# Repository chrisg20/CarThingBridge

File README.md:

# CarThingBridge
A compact connector board for the Spotify Car Thing and Raspberry Pi Zero, for use with [Nocturne](https://github.com/usenocturne/nocturne-image).

3D printed mount on Printables [here](https://www.printables.com/model/1098732-car-thing-pi-bridge).

# Ordering Instructions
I no longer sell the boards due to lower demand, high tariffs, etc. 

If you want one, it is worth asking on the Nocturne Discord server to see if other users have extra boards that they would be willing to give or sell to you. 

Server: https://discord.gg/GTP9AawHPt

To order boards yourself, follow these steps:

**Order PCB Only (Manual Assembly)**

Manual assembly should only be attempted if you are experienced in soldering very small (0603) components.

* Download the ZIP archive: https://github.com/chrisg20/CarThingBridge/PCB/production/.
* Visit https://JLCPCB.com and click Order Now.
* Upload Bridge_v1.zip from the PCB/production/ directory.
* VERY IMPORTANT! Set PCB Layers to 2 and Thickness to 0.8mm — this is required for the straddle-mounted USB-C connector.
* Order components from Digi-Key, Mouser, etc.
* Required Components (per PCB):
  * CX60-24S-UNIT (x1)
  * CX90M-16P (x1)
  * SSSS811101 (x1)
  * ZX60-B-5S(31) (x2)
  * 0603WAF5101T5E (x3)

**Order PCB with Assembly**

* Enable PCB Assembly during order setup.
* On the Bill of Materials page:
* Upload bom.csv from PCB/production/.
* Upload positions.csv from PCB/production/.
* Review the component placement preview to ensure it looks correct.

You will receive the a notification to pay an additional ~$50 for a fixture required for the USB-C connector (C5338340).

# Instructions

Print the mount and install 4 M2.5x3mm inserts into the holes. Place adhesive strips into the slots and attach to the car thing so that the Nocturne logo bar lines up with the left edge of the Car Thing as shown in the image below.

Connect the Raspberry Pi to the bridge and the bridge to the Car Thing. Secure the Raspberry Pi to the mount with 4 M2.5x4mm screws. Ensure the small switch is set to ON (away from the Raspberry Pi) as shown.

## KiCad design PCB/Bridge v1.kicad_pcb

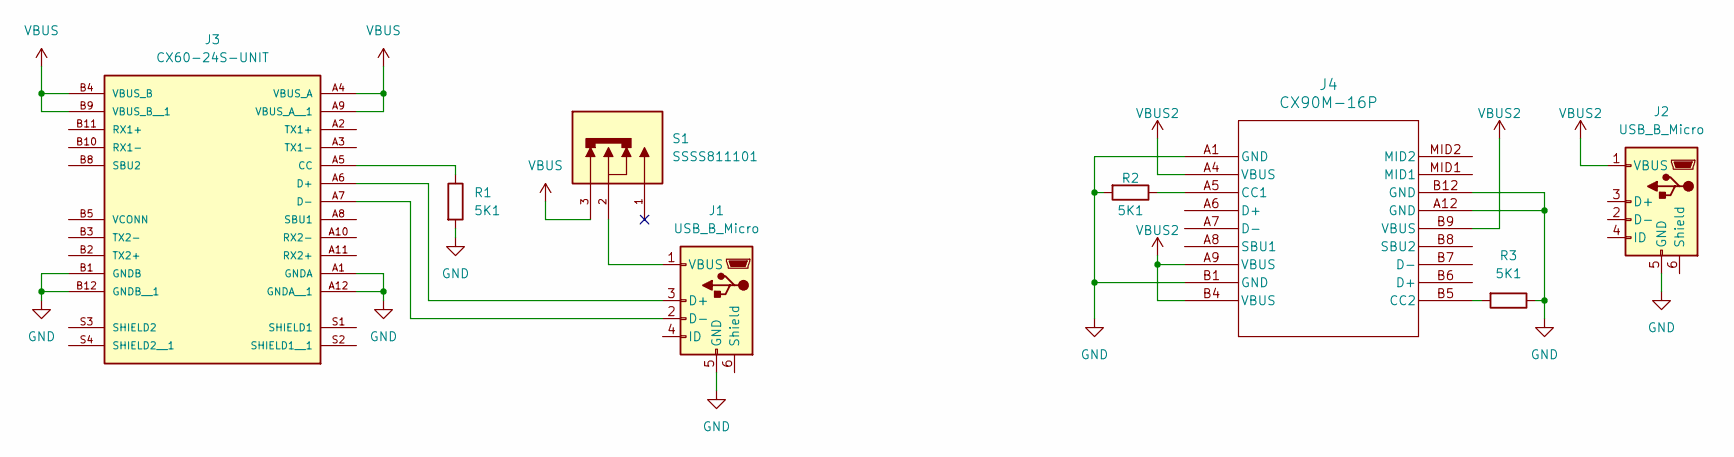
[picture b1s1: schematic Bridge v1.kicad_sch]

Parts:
J1, J2: USB_B_Micro; CONN_ZX60-B-5S31_HIR
J3: CX60-24S-UNIT; HIROSE_CX60-24S-UNIT; PARTREV 5
J4: CX90M-16P; CX90M-16P_HIR
R1, R2, R3: 5K1; R_0603_1608Metric
S1: SSSS811101; SW_SSSS811101; PARTREV N/A

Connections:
GND: J1.5 (GND), J2.5 (GND), J3.A1 (GNDA), J3.A12 (GNDA__1), J3.B1 (GNDB), J3.B12 (GNDB__1), J4.A1 (GND), J4.A12 (GND), J4.B1 (GND), J4.B12 (GND), R1.2, R2.2, R3.1
unnamed: J1.3 (D+), J3.A6 (D+)
unnamed: J1.2 (D-), J3.A7 (D-)
unnamed: J1.1 (VBUS), S1.2
unnamed: J3.A5 (CC), R1.1
unnamed: J4.A5 (CC1), R2.1
unnamed: J4.B5 (CC2), R3.2
VBUS: J3.A4 (VBUS_A), J3.A9 (VBUS_A__1), J3.B4 (VBUS_B), J3.B9 (VBUS_B__1), S1.3
VBUS2: J2.1 (VBUS), J4.A4 (VBUS), J4.A9 (VBUS), J4.B4 (VBUS), J4.B9 (VBUS)

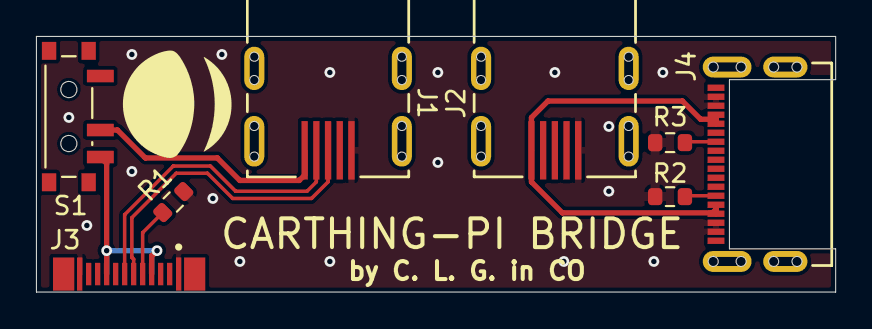
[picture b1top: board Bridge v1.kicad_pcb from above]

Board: 2 copper layers, 44.4 x 14.2 mm, 8 parts (0 on the bottom side), 9 nets.

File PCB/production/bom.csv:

Designator,Footprint,Quantity,Value,LCSC Part #
"J1, J2",CONN_ZX60-B-5S31_HIR,2,USB_B_Micro,
J3,HIROSE_CX60-24S-UNIT,1,CX60-24S-UNIT,
J4,CX90M-16P_HIR,1,CX90M-16P,
"R1, R2, R3",0603,3,5K1,
S1,SW_SSSS811101,1,SSSS811101,

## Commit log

2024-12-05 Create LICENSE
